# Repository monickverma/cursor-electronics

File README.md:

# Circuit OS

**Describe a circuit in plain English → get a validated schematic, Arduino firmware, a SPICE simulation, a bill of materials, and an explanation of every design choice.**

**Live demo: [circuit-os-ecru.vercel.app](https://circuit-os-ecru.vercel.app)** — runs in demo mode: five recorded designs (schematic, firmware, SPICE, BOM, validation) produced by the real deterministic pipeline via [`scripts/build_demo_fixtures.py`](scripts/build_demo_fixtures.py). Free-text design needs the backend; see [SETUP.md](SETUP.md).

Circuit OS is an AI hardware compiler. It runs on Claude or on **open models served by vLLM on AMD ROCm GPUs** — see [docs/AMD.md](docs/AMD.md).

## The one rule

> The LLM never writes SPICE, KiCad files or firmware directly.

LLMs invent pin numbers and function names. So the model only outputs structured JSON against a strict intermediate representation (IR) schema, and deterministic compilers do everything else:

```
prompt ─► intent parser ─► circuit reasoner ─► IR (JSON)
                                  ▲               │
                                  │   Pydantic + hardware rule engine
                                  └── exact field errors, ≤3 retries
                                                  │
                     ┌──────────────┬─────────────┼──────────────┬───────────┐
                  ngspice        KiCad        Arduino .ino       BOM     explanation
                 simulation    schematic     (Jinja2, compiles)
                 (pass/fail, 15% tolerance)
```

Same input, same output. A wrong part — say 1nF instead of 100nF in an RC filter — fails simulation before anything is built.

## Features

- **Hardware rule engine** — floating nodes, voltage ratings, missing I²C pull-ups, RS-485 termination, PWM-capable pins
- **Simulation** — ngspice runs in the background (Celery + Redis), graded pass/fail
- **Patching** — "make the LED brighter" becomes a small patch that changes only what was asked
- **Explanations that focus on consequences** — not "R3 limits current", but what breaks if you change R3
- **Runs on AMD** — the same pipeline runs on an open model served by vLLM on ROCm, with a benchmark script
- JWT auth, rate limiting, PostgreSQL storage, 400+ passing tests
- Experimental PCB layout engine with an A* router

**v0.1.0 templates:** DHT22 sensor alert · MAX485 Modbus RTU · LED with current-limiting resistor · RC low-pass filter · voltage divider

## Stack

FastAPI · Pydantic v2 · Anthropic SDK / vLLM (OpenAI-compatible) · ngspice · Celery + Redis · PostgreSQL · Next.js · Jinja2

## Quick start

See [SETUP.md](SETUP.md). Short version:

```bash
cp .env.example .env        # set ANTHROPIC_API_KEY, or AI_PROVIDER=openai_compat for vLLM
docker-compose up -d        # PostgreSQL + Redis
pip install -r backend/requirements.txt
python -m pytest -q
start.bat                   # backend + frontend on Windows
```

### On AMD GPUs

```bash
vllm serve Qwen/Qwen2.5-7B-Instruct --port 8000 --enable-auto-tool-choice --tool-call-parser hermes
AI_PROVIDER=openai_compat AI_MODEL=Qwen/Qwen2.5-7B-Instruct python scripts/amd_benchmark.py
```

Full guide: [docs/AMD.md](docs/AMD.md).

## Roadmap

Free-form circuits beyond the five templates. See [ROADMAP.md](ROADMAP.md).

## License

Copyright (C) 2026 Monick Verma.

Circuit OS is free and open-source software under the **GNU Affero General Public License v3.0** — see [LICENSE](LICENSE). If you modify it, or run a modified version as a network service, you must release your source under the same license. For commercial licensing under different terms, contact the author.

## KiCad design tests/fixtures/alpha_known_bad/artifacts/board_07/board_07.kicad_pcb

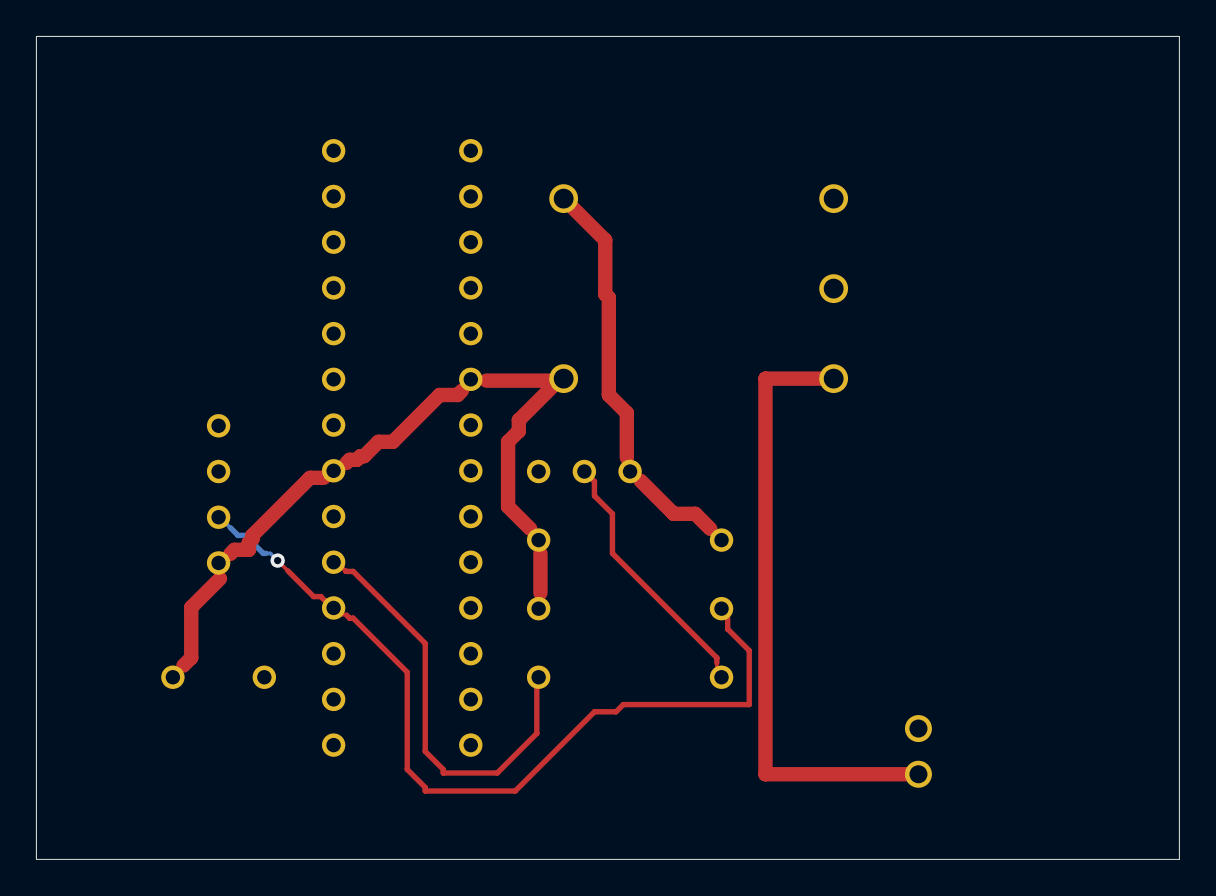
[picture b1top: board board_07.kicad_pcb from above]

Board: 2 copper layers, 63.5 x 45.7 mm, 9 parts (0 on the bottom side), 7 nets.

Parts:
C1: K104K15X7RF53H5; RADIAL-2
D1: 1N4007; DO-41
J1: 22-27-2021; HEADER-2
K1: SRD-05VDC-SL-C; RELAY-SRD
Q1: 2N2222A; TO-92
R1: CFR-25JB-52-10K; AXIAL
R2: CFR-25JB-52-1K; AXIAL
U1: ATMEGA328P-PU; DIP-28
U2: DHT22

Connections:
DHT22_DATA: R1.2, U1.4, U2.2
GND: C1.2, Q1.1, U1.8, U1.22, U2.4
MAINS_L: J1.1, K1.3
RELAY_COIL_NEG: D1.2, K1.2, Q1.3
RELAY_CTRL: Q1.2, R2.2
TRANSISTOR_BASE: R2.1, U1.5
VCC_5V: C1.1, D1.1, K1.1, R1.1, U1.7, U1.20, U2.1

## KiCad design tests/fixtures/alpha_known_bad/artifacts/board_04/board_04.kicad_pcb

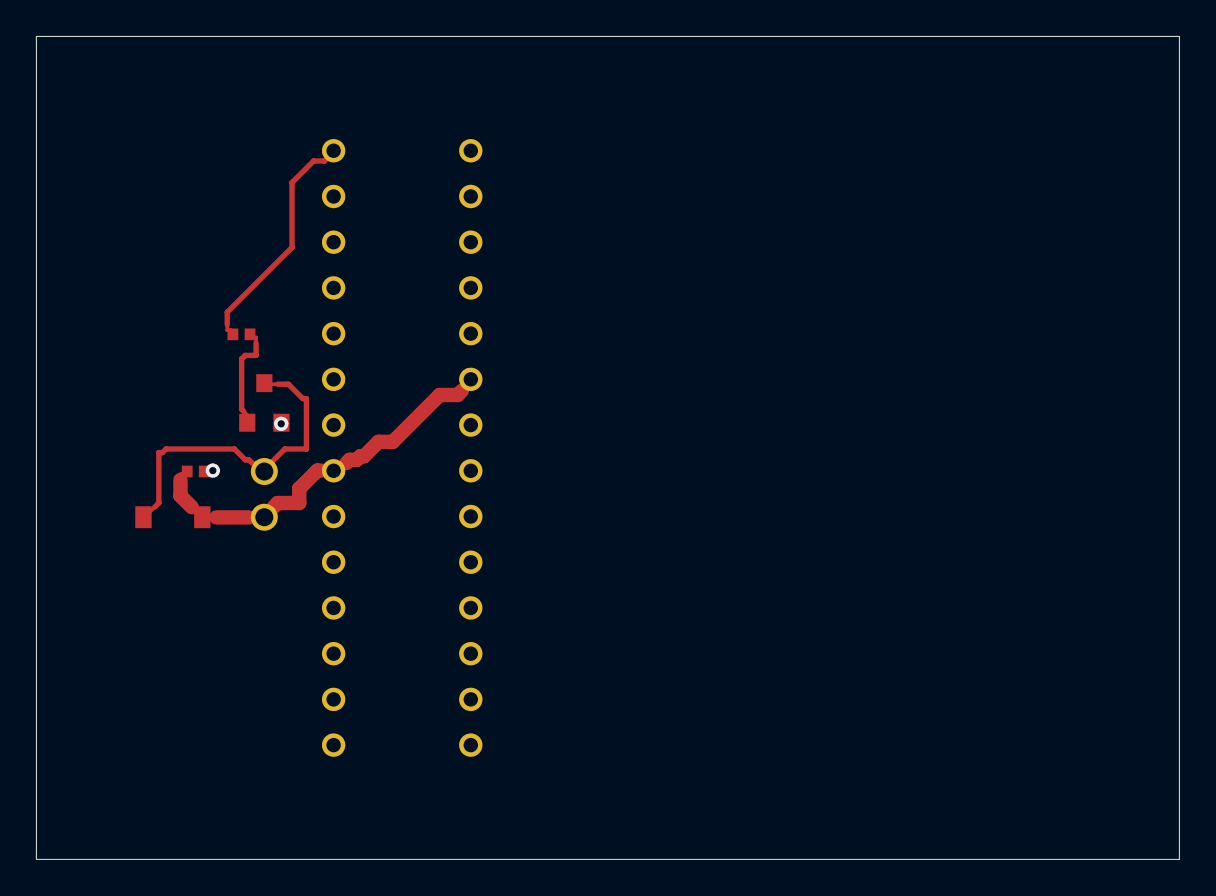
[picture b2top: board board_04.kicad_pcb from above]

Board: 2 copper layers, 63.5 x 45.7 mm, 6 parts (0 on the bottom side), 5 nets.

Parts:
C1: 100nF; 0402
D1: 1N4148W-7-F; SOD-123
J1: 166.667; HEADER-2
Q1: MMBT2222ALT1G; SOT-23
R1: 1210; 0402
U1: ATmega328P-PU; DIP-28

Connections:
GND: C1.2, Q1.2, U1.8, U1.22
SW_BASE: Q1.1, R1.2
SW_CTRL: R1.1, U1.14
SW_LOAD: D1.1, J1.2, Q1.3
VCC_5V: C1.1, D1.2, J1.1, U1.7, U1.20

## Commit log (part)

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2025-09-20 first
2026-06-03 chore: integrate project brain scaffold for Circuit OS
    - Customize brain/ with Circuit OS vision, architecture, decisions, knowledge, timeline
    - Customize plan/ with 5-phase roadmap and Phase 1 hardware copilot gate
    - Update tools/regen_state.py to track real backend modules and 5 phases
    - Update tools/progress_gen.py to scan backend/ and track AI/simulation functions
    - Add UTF-8 encoding fixes for Windows terminal Unicode issues
    - Project now tracks Circuit OS state via state.json and progress.yaml
